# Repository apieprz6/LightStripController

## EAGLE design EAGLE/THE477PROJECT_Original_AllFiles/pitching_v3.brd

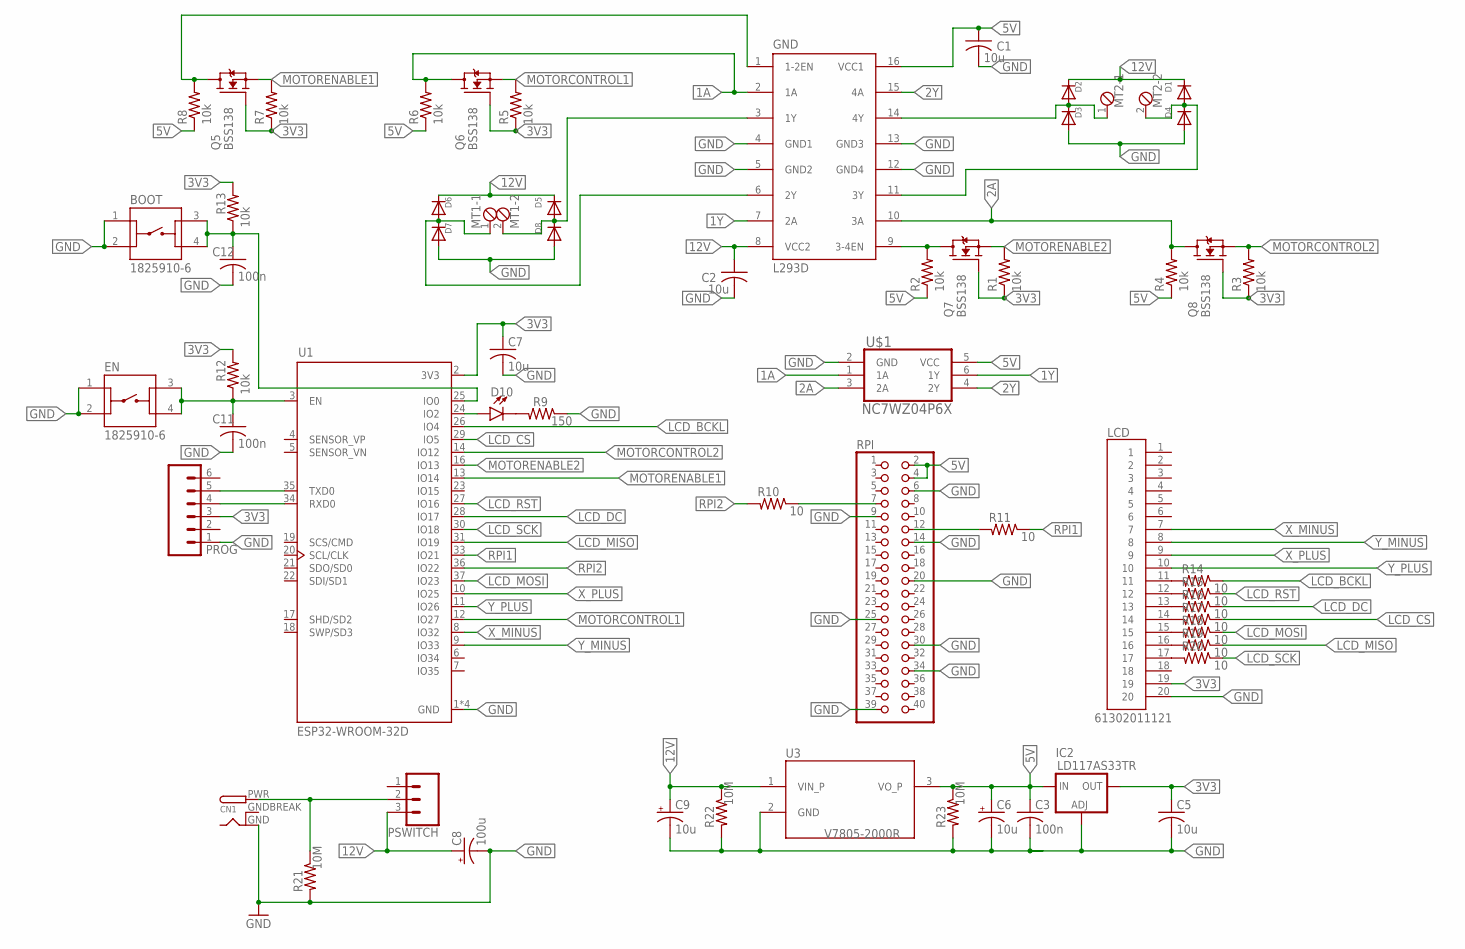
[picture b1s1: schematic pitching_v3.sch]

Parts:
BOOT: 1825910-6
C1, C2, C5, C7: 10u; C0805
C3, C11, C12: 100n; C0805
C6, C9: 10u; 153CLV-0405
C8: 100u; 153CLV-0810
CN1: DCBARRELPTH; DCJACK_2MM_PTH
D1, D2, D3, D4, D5, D6, D7, D8: DIODESMA; SMADIODE
D10: LED3MM; LED_3MM
EN: 1825910-6
GND: L293D; DIL16
IC2: LD117AS33TR; SOT223
LCD: 61302011121
MT1, MT2: MPT2; 2POL254
PROG: CONN_06SILK_FEMALE_PTH; 1X06
PSWITCH: CONN_03; 1X03
Q5, Q6, Q7, Q8: BSS138; SOT23
R1, R2, R3, R4, R5, R6, R7, R8, R12, R13: 10k; R0805
R9: 150; R0805
R10, R11, R14, R15, R16, R17, R18, R19, R20: 10; R0805
R21, R22, R23: 10M; R1206
RPI: PINHD-2X20; 2X20
U1: ESP32-WROOM-32D; MODULE_ESP32-WROOM-32D
U3: V7805-2000R; CONV_V7805-2000R
U$1: NC7WZ04P6X; SOT65P210X110-6N

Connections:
1A: GND.2 (1A), Q6.3 (D), R6.2, U$1.1 (1A)
1Y: GND.7 (2A), U$1.6 (1Y)
2A: GND.10 (3A), Q8.3 (D), R4.2, U$1.3 (2A)
2Y: GND.15 (4A), U$1.4 (2Y)
3V3: C5.1, C7.1, IC2.4 (OUT), LCD.19, PROG.3, Q5.1 (G), Q6.1 (G), Q7.1 (G), Q8.1 (G), R1.1, R3.1, R5.1, R7.1, R12.2, R13.2, U1.2 (3V3)
5V: C1.1, C3.1, C6.+, GND.16 (VCC1), IC2.3 (IN), R2.1, R4.1, R6.1, R8.1, R23.1, RPI.2, RPI.4, U3.3 (VO_P), U$1.5 (VCC)
12V: C2.1, C8.+, C9.+, D1.C, D2.C, D5.C, D6.C, GND.8 (VCC2), PSWITCH.3, R22.1, U3.1 (VIN_P)
BOOT: BOOT.3, BOOT.4, C12.1, R13.1, U1.25 (IO0)
EN: C11.1, EN.3, EN.4, R12.1, U1.3 (EN)
GND: BOOT.1, BOOT.2, C1.2, C2.2, C3.2, C5.2, C6.-, C7.2, C8.-, C9.-, C11.2, C12.2, CN1.GND, D3.A, D4.A, D7.A, D8.A, EN.1, EN.2, GND.4 (GND1), GND.5 (GND2), GND.12 (GND4), GND.13 (GND3), IC2.1 (ADJ), LCD.20, PROG.1, R9.1, R21.2, R22.2, R23.2, RPI.6, RPI.9, RPI.14, RPI.20, RPI.25, RPI.30, RPI.34, RPI.39, U1.1 (GND), U1.15 (GND), U1.38 (GND), U1.39 (GND), U3.2 (GND), U$1.2 (GND)
GNDBREAK: CN1.GNDBREAK
LCD_BCKL: R14.1, U1.26 (IO4)
LCD_CS: R17.1, U1.29 (IO5)
LCD_DC: R16.1, U1.28 (IO17)
LCD_MISO: R19.1, U1.31 (IO19)
LCD_MOSI: R18.1, U1.37 (IO23)
LCD_RST: R15.1, U1.27 (IO16)
LCD_SCK: R20.1, U1.30 (IO18)
M1+: D5.A, D8.C, GND.3 (1Y), MT1.2
M1-: D6.A, D7.C, GND.6 (2Y), MT1.1
M2+: D1.A, D4.C, GND.11 (3Y), MT2.2
M2-: D2.A, D3.C, GND.14 (4Y), MT2.1
MOTORCONTROL1: Q6.2 (S), R5.2, U1.12 (IO27)
MOTORCONTROL2: Q8.2 (S), R3.2, U1.14 (IO12)
MOTORENABLE1: Q5.2 (S), R7.2, U1.13 (IO14)
MOTORENABLE2: Q7.2 (S), R1.2, U1.16 (IO13)
unnamed: CN1.PWR, PSWITCH.2, R21.1
unnamed: R11.2, RPI.12
unnamed: LCD.11, R14.2
unnamed: R10.1, RPI.7
unnamed: LCD.12, R15.2
unnamed: LCD.13, R16.2
unnamed: GND.1 (1-2EN), Q5.3 (D), R8.2
unnamed: GND.9 (3-4EN), Q7.3 (D), R2.2
unnamed: D10.K (C), R9.2
unnamed: LCD.14, R17.2
unnamed: LCD.15, R18.2
unnamed: PROG.5, U1.35 (TXD0)
unnamed: LCD.16, R19.2
unnamed: LCD.17, R20.2
unnamed: PROG.4, U1.34 (RXD0)
unnamed: D10.A, U1.24 (IO2)
RPI1: R11.1, U1.33 (IO21)
RPI2: R10.2, U1.36 (IO22)
X_MINUS: LCD.7, U1.8 (IO32)
X_PLUS: LCD.9, U1.10 (IO25)
Y_MINUS: LCD.8, U1.9 (IO33)
Y_PLUS: LCD.10, U1.11 (IO26)

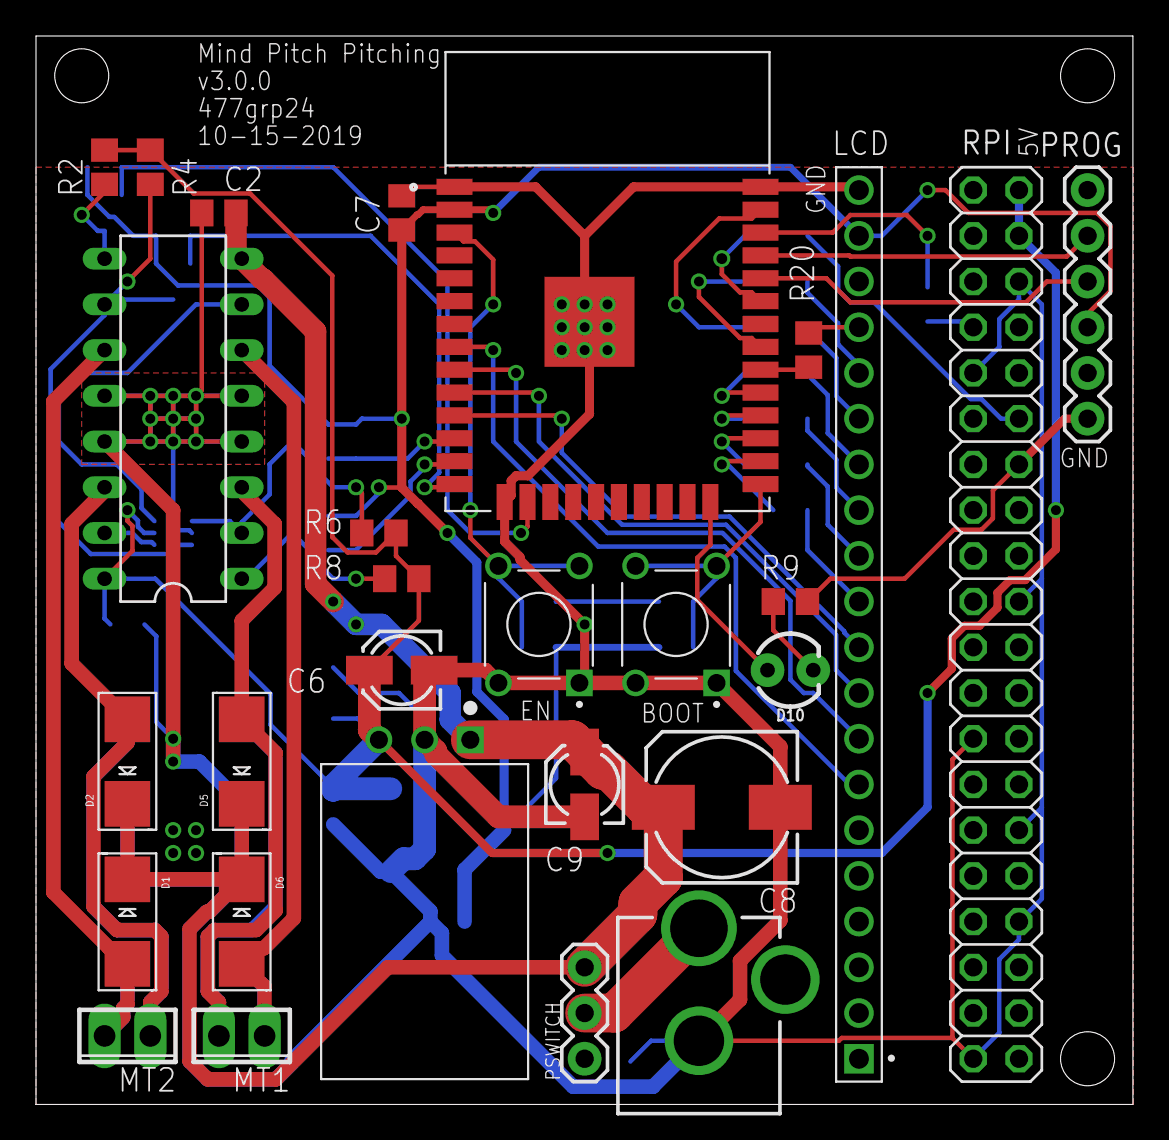
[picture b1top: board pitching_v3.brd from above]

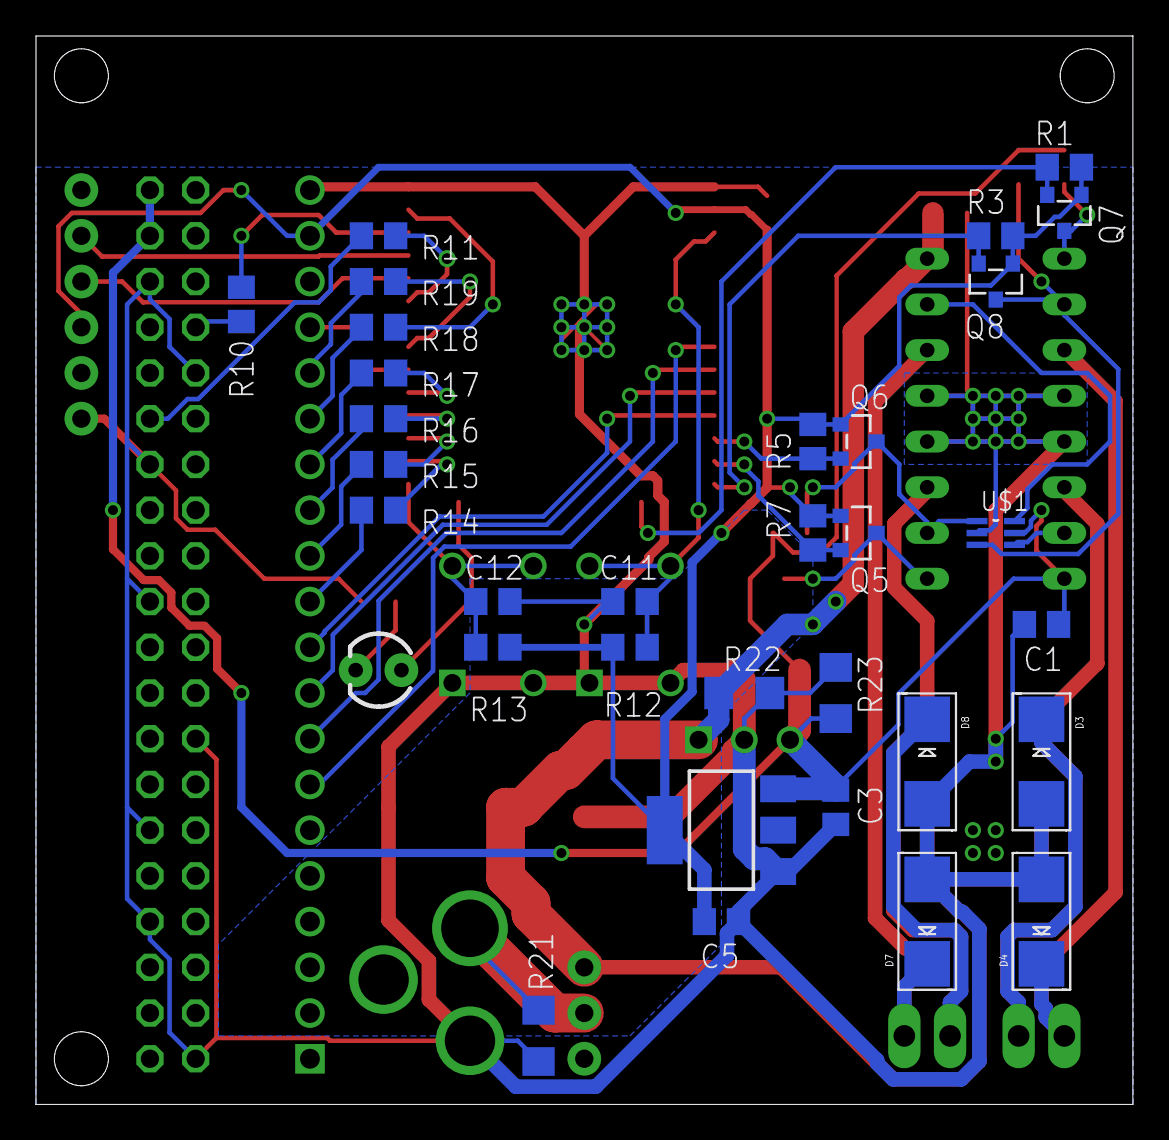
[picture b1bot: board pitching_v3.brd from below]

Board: 2 copper layers, 60.9 x 59.4 mm, 60 parts (32 on the bottom side), 47 nets.

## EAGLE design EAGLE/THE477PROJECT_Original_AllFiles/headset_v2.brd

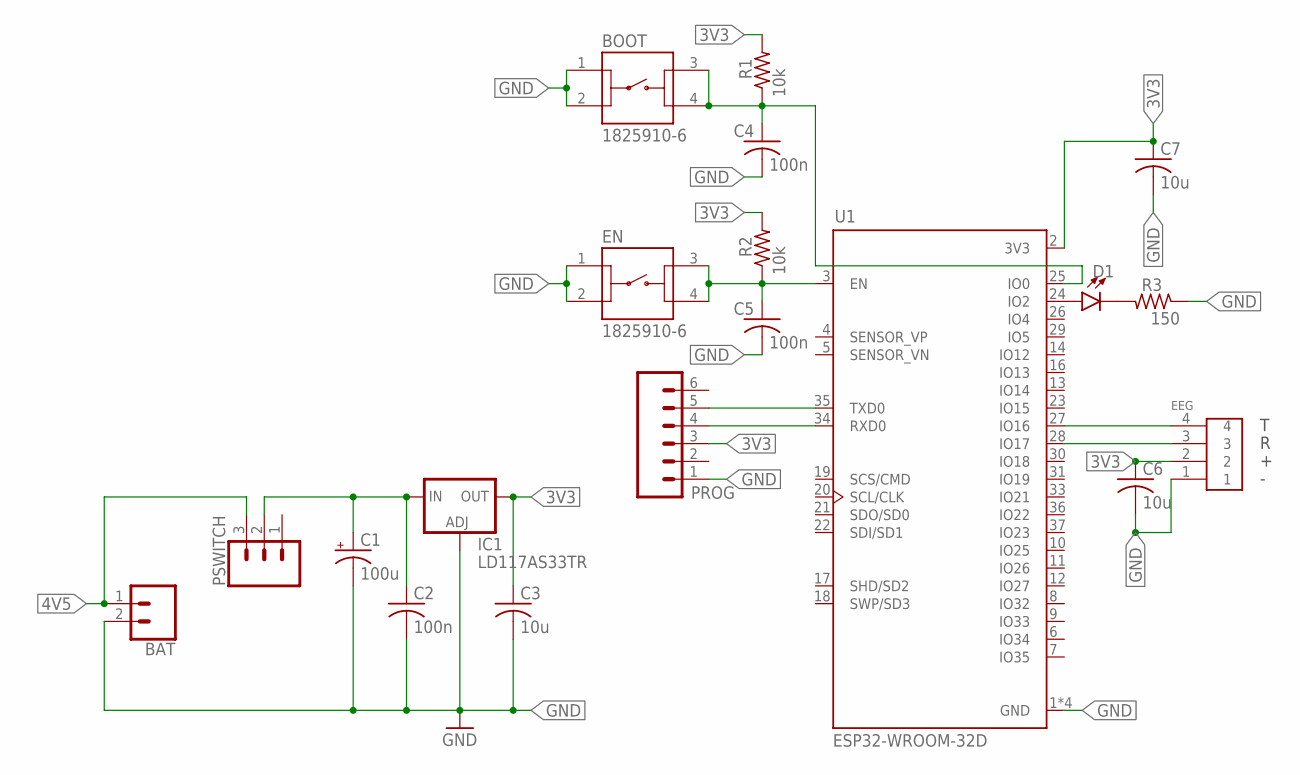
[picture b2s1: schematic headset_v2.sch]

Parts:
BAT: CONN_02; 1X02
BOOT: 1825910-6
C1: 100u; 153CLV-0810
C2, C4, C5: 100n; C0805
C3, C6, C7: 10u; C0805
D1: LED3MM; LED_3MM
EEG: 2PIN; B2B-PH-K-S
EN: 1825910-6
IC1: LD117AS33TR; SOT223
PROG: CONN_06SILK_FEMALE_PTH; 1X06
PSWITCH: CONN_03; 1X03
R1, R2: 10k; R0805
R3: 150; R0805
U1: ESP32-WROOM-32D; MODULE_ESP32-WROOM-32D

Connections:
3V3: C3.1, C6.1, C7.1, EEG.2, IC1.4 (OUT), PROG.3, R1.2, R2.2, U1.2 (3V3)
4V5: BAT.1, PSWITCH.3
GND: BAT.2, BOOT.1, BOOT.2, C1.-, C2.2, C3.2, C4.2, C5.2, C6.2, C7.2, EEG.1, EN.1, EN.2, IC1.1 (ADJ), PROG.1, R3.1, U1.1 (GND), U1.15 (GND), U1.38 (GND), U1.39 (GND)
unnamed: PROG.5, U1.35 (TXD0)
unnamed: PROG.4, U1.34 (RXD0)
unnamed: C1.+, C2.1, IC1.3 (IN), PSWITCH.2
unnamed: D1.A, U1.24 (IO2)
unnamed: EEG.3, U1.28 (IO17)
unnamed: EEG.4, U1.27 (IO16)
unnamed: D1.K (C), R3.2
unnamed: C5.1, EN.3, EN.4, R2.1, U1.3 (EN)
unnamed: BOOT.3, BOOT.4, C4.1, R1.1, U1.25 (IO0)

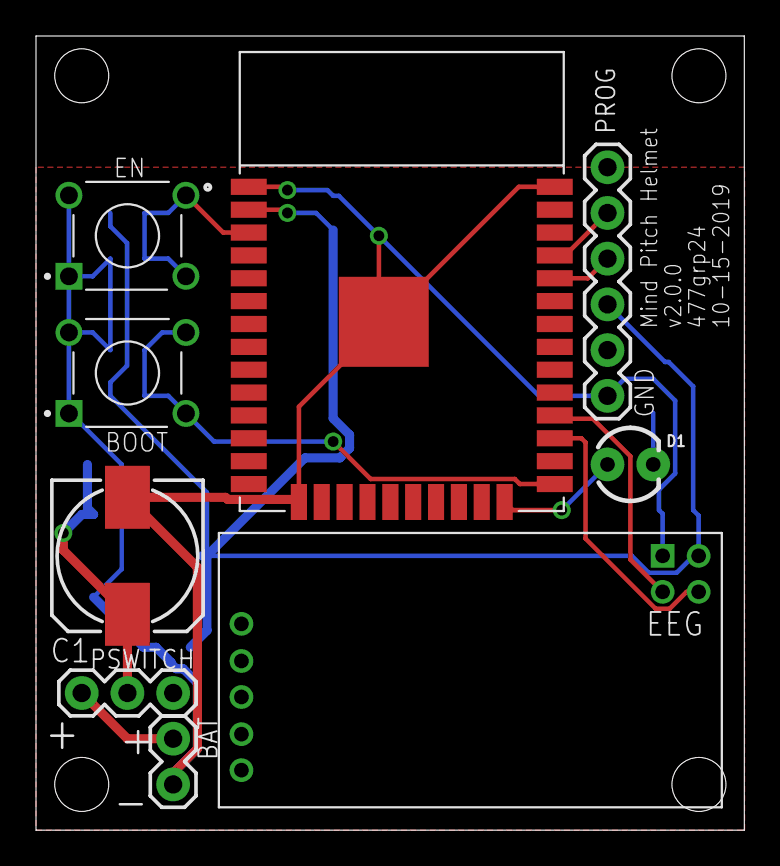
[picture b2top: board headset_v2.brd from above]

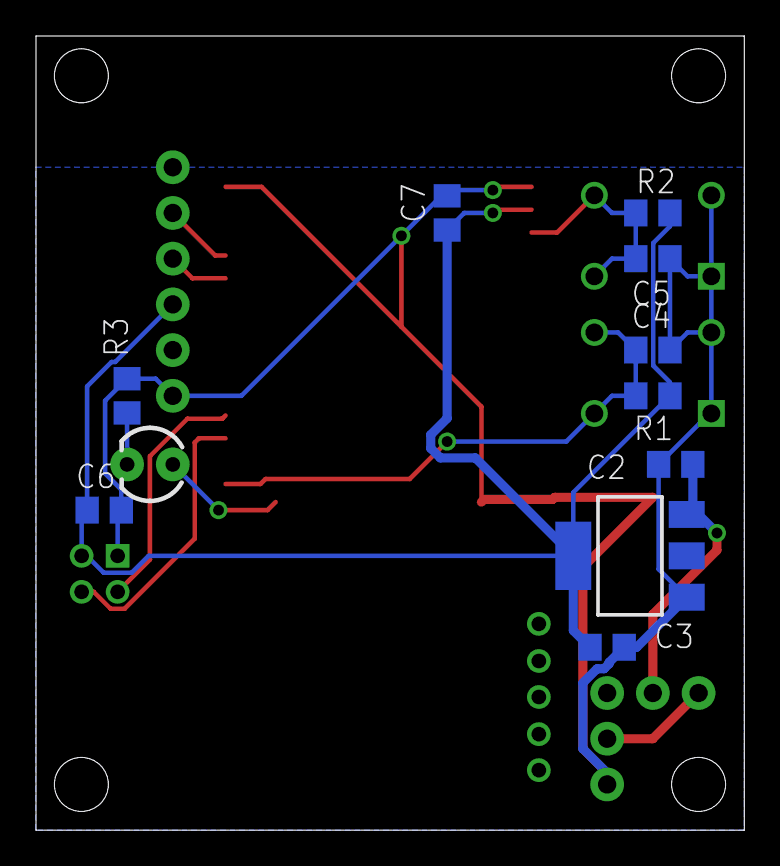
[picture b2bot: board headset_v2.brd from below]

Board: 2 copper layers, 39.4 x 44.1 mm, 19 parts (10 on the bottom side), 12 nets.

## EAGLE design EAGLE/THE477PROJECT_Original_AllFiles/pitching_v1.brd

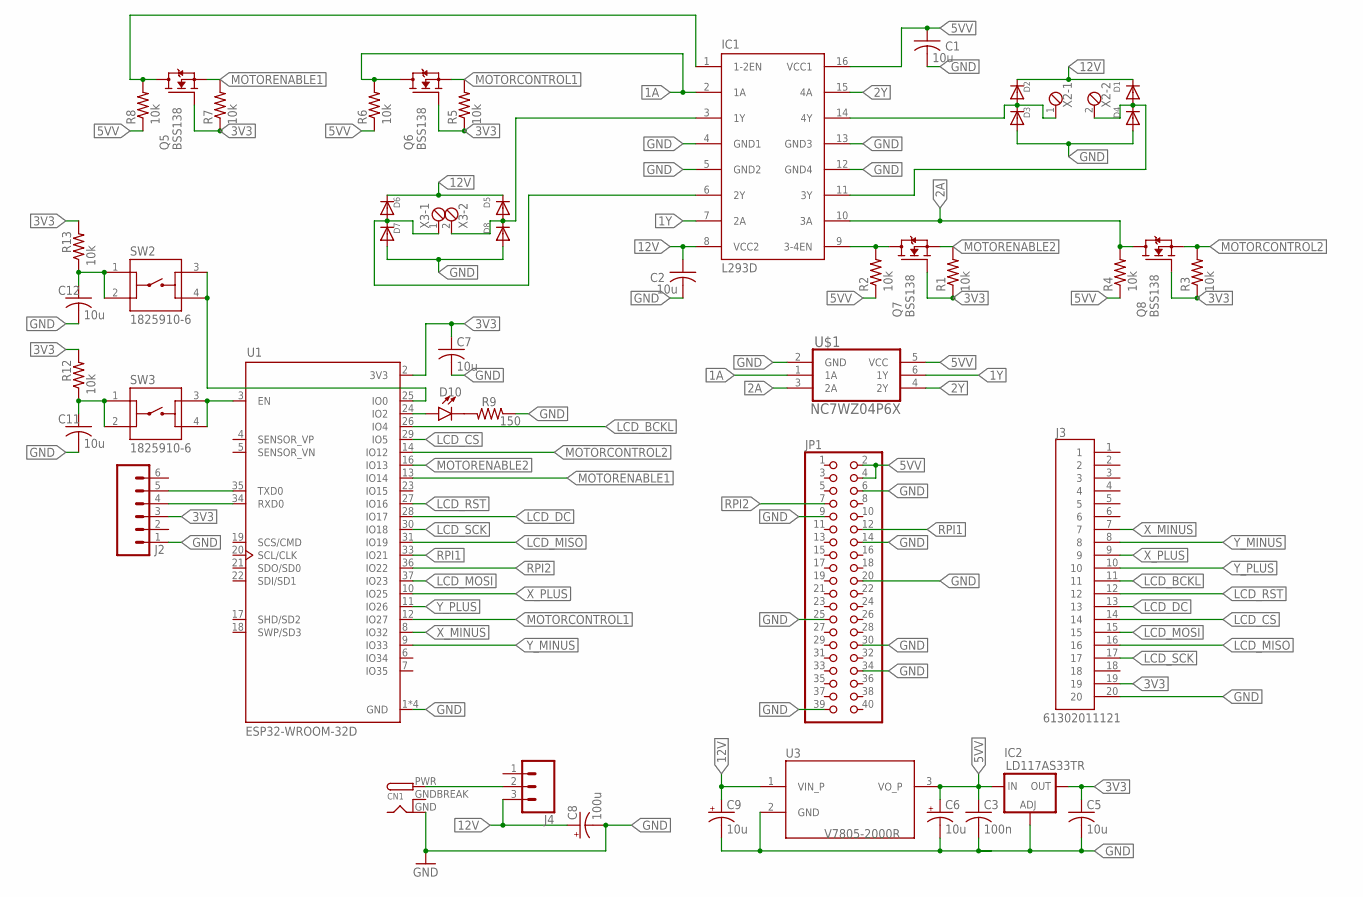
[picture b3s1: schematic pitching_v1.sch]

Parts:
C1, C2, C5, C7, C11, C12: 10u; C0805
C3: 100n; C0805
C6, C9: 10u; 153CLV-0405
C8: 100u; 153CLV-0810
CN1: DCBARRELPTH; DCJACK_2MM_PTH
D1, D2, D3, D4, D5, D6, D7, D8: DIODESMA; SMADIODE
D10: LED3MM; LED_3MM
IC1: L293D; DIL16
IC2: LD117AS33TR; SOT223
J2: CONN_06NO_SILK_FEMALE_PTH; 1X06_NO_SILK
J3: 61302011121
J4: CONN_03; 1X03
JP1: PINHD-2X20; 2X20
Q5, Q6, Q7, Q8: BSS138; SOT23
R1, R2, R3, R4, R5, R6, R7, R8, R12, R13: 10k; R0805
R9: 150; R0805
SW2, SW3: 1825910-6
U1: ESP32-WROOM-32D; MODULE_ESP32-WROOM-32D
U3: V7805-2000R; CONV_V7805-2000R
U$1: NC7WZ04P6X; SOT65P210X110-6N
X2, X3: MPT2; 2POL254

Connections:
1A: IC1.2 (1A), Q6.3 (D), R6.2, U$1.1 (1A)
1Y: IC1.7 (2A), U$1.6 (1Y)
2A: IC1.10 (3A), Q8.3 (D), R4.2, U$1.3 (2A)
2Y: IC1.15 (4A), U$1.4 (2Y)
3V3: C5.1, C7.1, IC2.4 (OUT), J2.3, J3.19, Q5.1 (G), Q6.1 (G), Q7.1 (G), Q8.1 (G), R1.1, R3.1, R5.1, R7.1, R12.2, R13.2, U1.2 (3V3)
5VV: C1.1, C3.1, C6.+, IC1.16 (VCC1), IC2.3 (IN), JP1.2, JP1.4, R2.1, R4.1, R6.1, R8.1, U3.3 (VO_P), U$1.5 (VCC)
12V: C2.1, C8.+, C9.+, D1.C, D2.C, D5.C, D6.C, IC1.8 (VCC2), J4.3, U3.1 (VIN_P)
GND: C1.2, C2.2, C3.2, C5.2, C6.-, C7.2, C8.-, C9.-, C11.2, C12.2, CN1.GND, D3.A, D4.A, D7.A, D8.A, IC1.4 (GND1), IC1.5 (GND2), IC1.12 (GND4), IC1.13 (GND3), IC2.1 (ADJ), J2.1, J3.20, JP1.6, JP1.9, JP1.14, JP1.20, JP1.25, JP1.30, JP1.34, JP1.39, R9.1, U1.1 (GND), U1.15 (GND), U1.38 (GND), U1.39 (GND), U3.2 (GND), U$1.2 (GND)
GNDBREAK: CN1.GNDBREAK
LCD_BCKL: J3.11, U1.26 (IO4)
LCD_CS: J3.14, U1.29 (IO5)
LCD_DC: J3.13, U1.28 (IO17)
LCD_MISO: J3.16, U1.31 (IO19)
LCD_MOSI: J3.15, U1.37 (IO23)
LCD_RST: J3.12, U1.27 (IO16)
LCD_SCK: J3.17, U1.30 (IO18)
MOTORCONTROL1: Q6.2 (S), R5.2, U1.12 (IO27)
MOTORCONTROL2: Q8.2 (S), R3.2, U1.14 (IO12)
MOTORENABLE1: Q5.2 (S), R7.2, U1.13 (IO14)
MOTORENABLE2: Q7.2 (S), R1.2, U1.16 (IO13)
unnamed: CN1.PWR, J4.2
unnamed: D6.A, D7.C, IC1.6 (2Y), X3.1
unnamed: D5.A, D8.C, IC1.3 (1Y), X3.2
unnamed: D2.A, D3.C, IC1.14 (4Y), X2.1
unnamed: D1.A, D4.C, IC1.11 (3Y), X2.2
unnamed: IC1.1 (1-2EN), Q5.3 (D), R8.2
unnamed: IC1.9 (3-4EN), Q7.3 (D), R2.2
unnamed: SW2.3, SW2.4, U1.25 (IO0)
unnamed: D10.K (C), R9.2
unnamed: J2.5, U1.35 (TXD0)
unnamed: J2.4, U1.34 (RXD0)
unnamed: C11.1, R12.1, SW3.1, SW3.2
unnamed: C12.1, R13.1, SW2.1, SW2.2
unnamed: D10.A, U1.24 (IO2)
unnamed: SW3.3, SW3.4, U1.3 (EN)
RPI1: JP1.12, U1.33 (IO21)
RPI2: JP1.7, U1.36 (IO22)
X_MINUS: J3.7, U1.8 (IO32)
X_PLUS: J3.9, U1.10 (IO25)
Y_MINUS: J3.8, U1.9 (IO33)
Y_PLUS: J3.10, U1.11 (IO26)

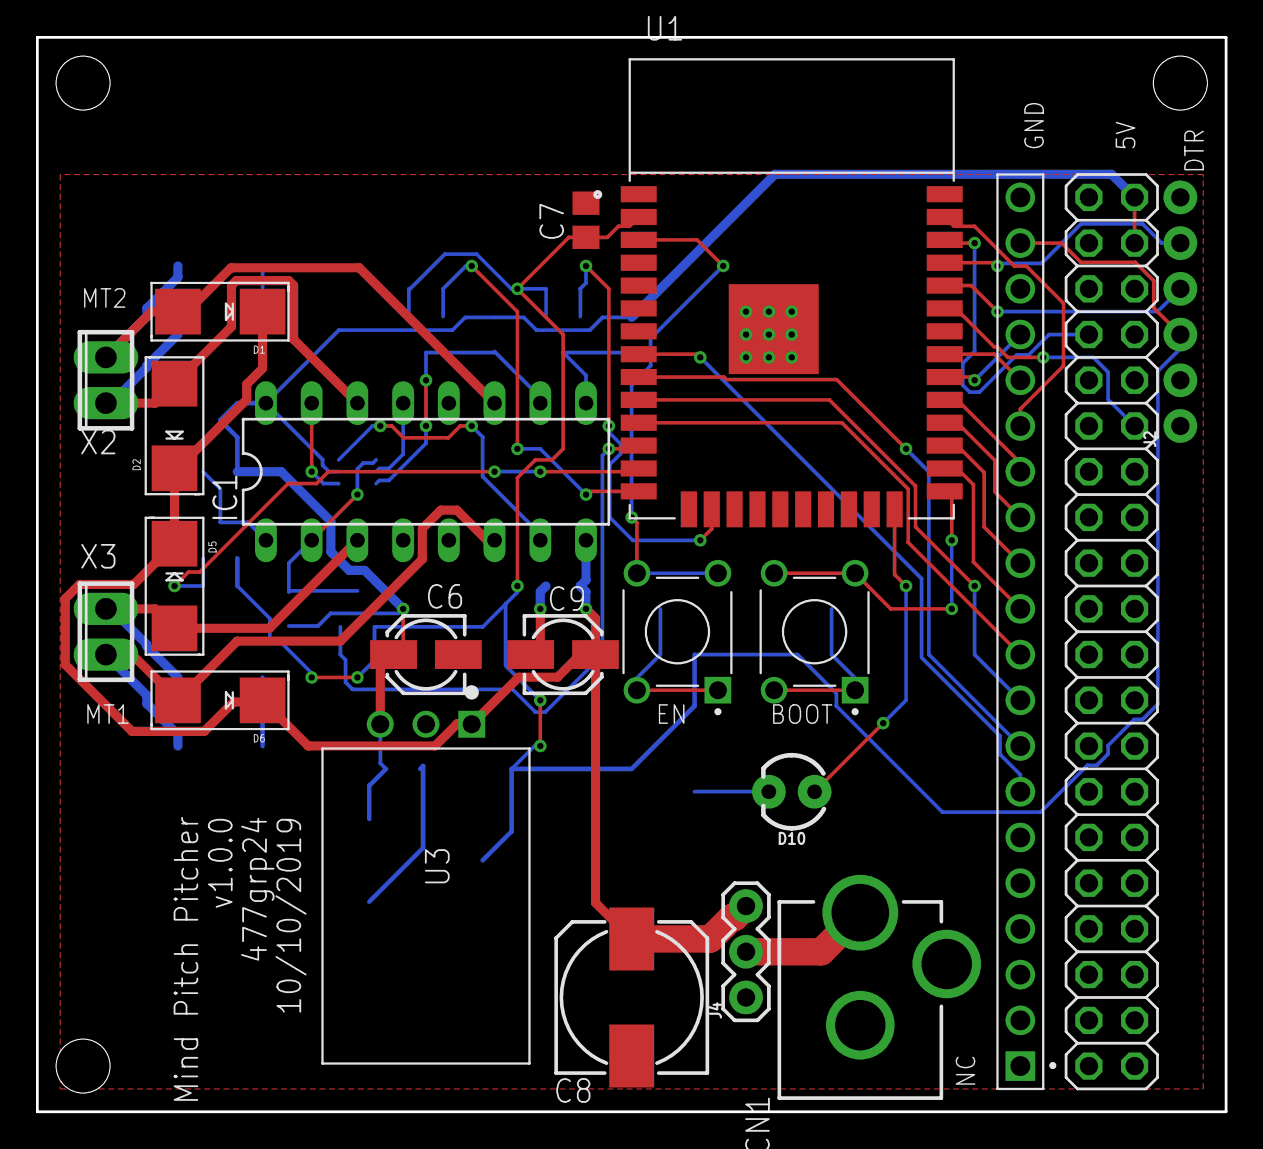
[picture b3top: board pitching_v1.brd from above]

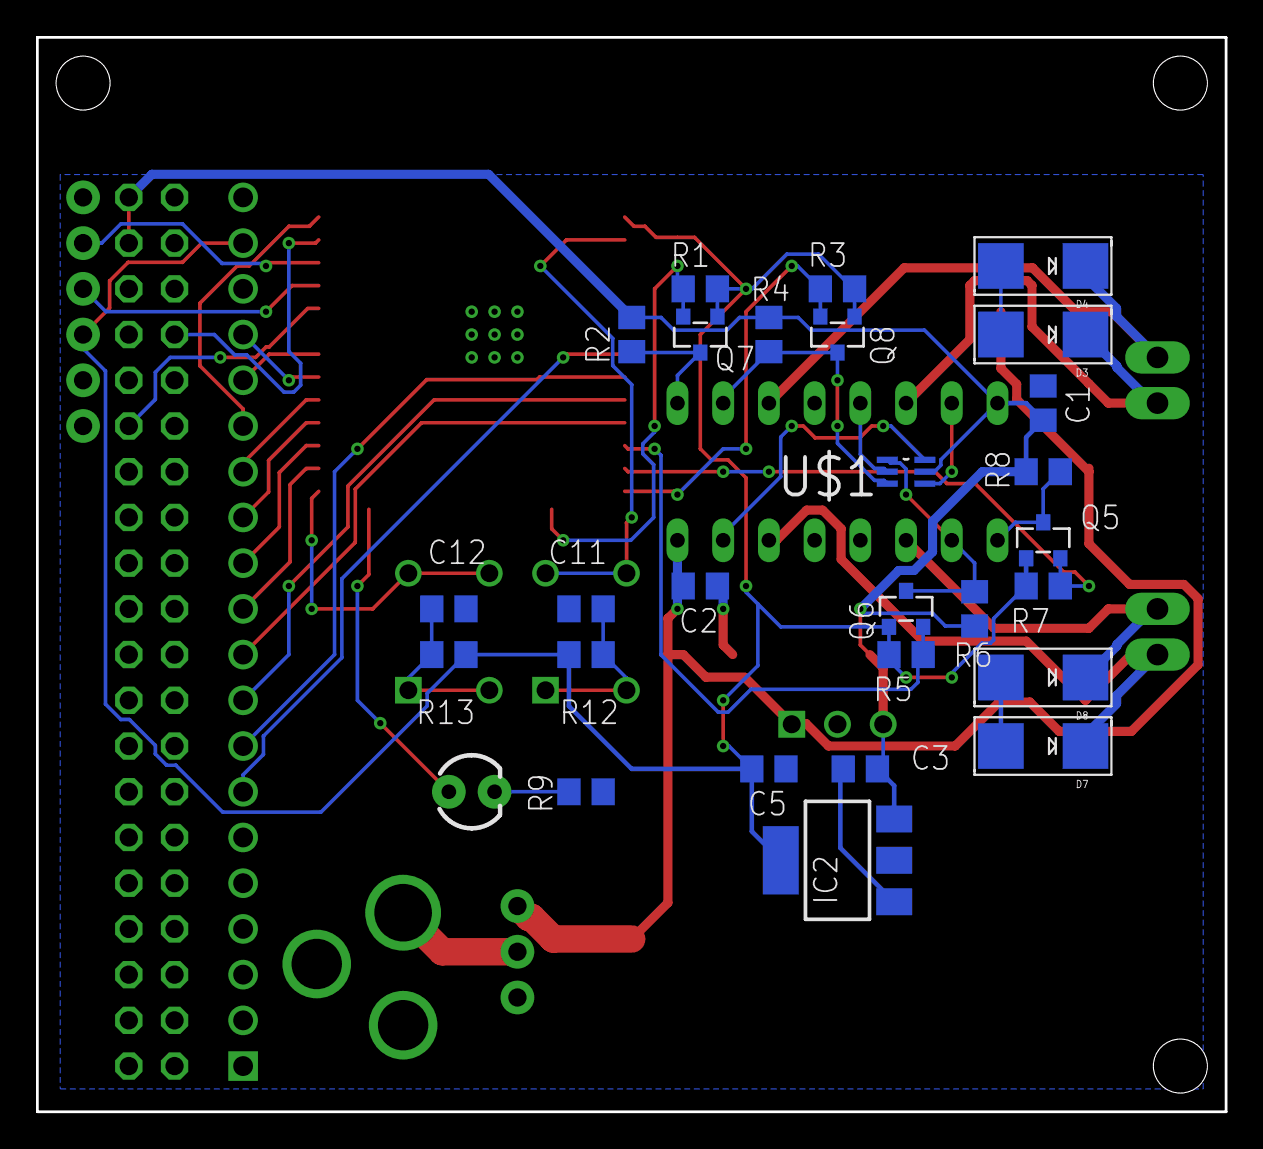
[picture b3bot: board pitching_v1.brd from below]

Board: 2 copper layers, 66.0 x 59.7 mm, 48 parts (27 on the bottom side), 40 nets.

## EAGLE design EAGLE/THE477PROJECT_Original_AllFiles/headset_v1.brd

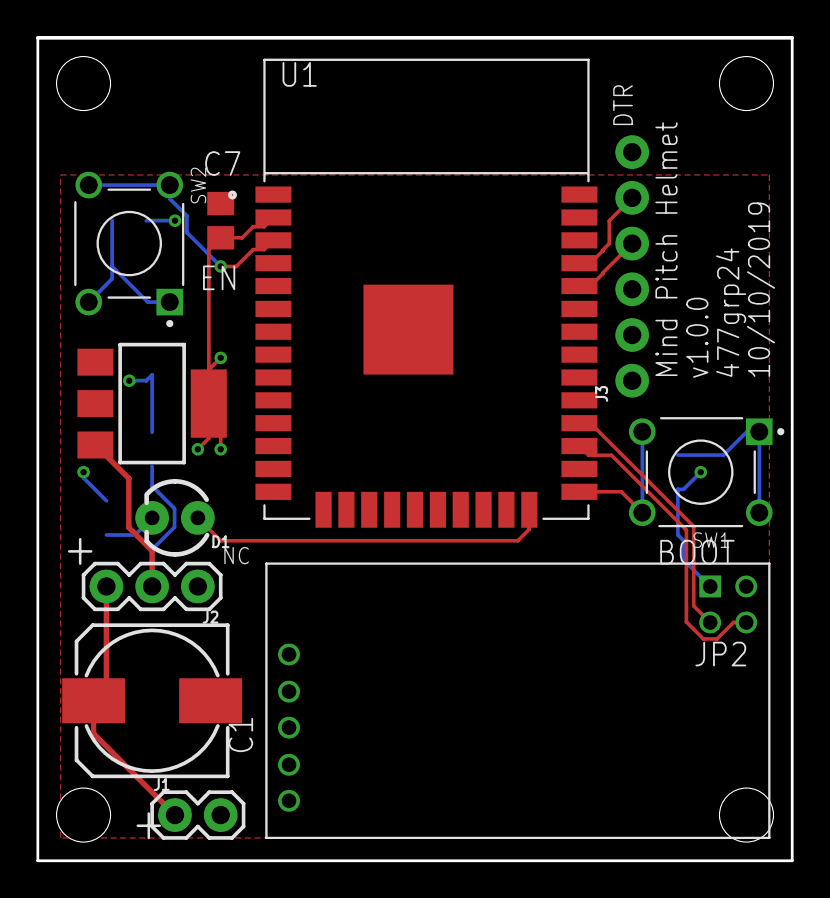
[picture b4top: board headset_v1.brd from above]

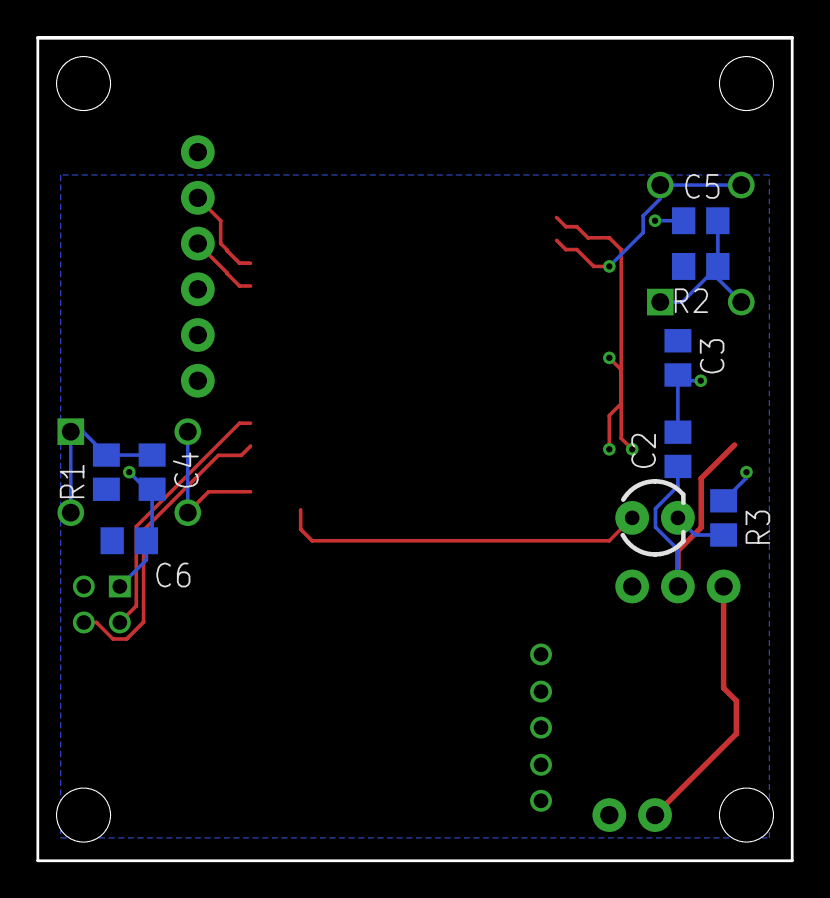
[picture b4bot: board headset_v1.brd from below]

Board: 2 copper layers, 41.9 x 45.7 mm, 19 parts (8 on the bottom side), 14 nets.

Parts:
C1: 100u; 153CLV-0810
C2: 100n; C0805
C3, C4, C5, C6, C7: 10u; C0805
D1: LED_3MM
IC1: LD117AS33TR; SOT223
J1: 1X02
J2: 1X03
J3: 1X06_NO_SILK
JP2: 2PIN; B2B-PH-K-S
R1, R2: 10k; R0805
R3: 150; R0805
SW1, SW2: 1825910-6
U1: ESP32-WROOM-32D; MODULE_ESP32-WROOM-32D

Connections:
3V3: C3.1, C6.1, C7.1, IC1.4, J3.3, JP2.2, R1.2, R2.2, U1.2
4V5: C1.+, J1.1, J2.3
GND: C1.-, C2.2, C3.2, C4.2, C5.2, C6.2, C7.2, IC1.1, J1.2, J3.1, JP2.1, R3.1, U1.1, U1.15, U1.38, U1.39
unnamed: J3.5, U1.35
unnamed: J3.4, U1.34
unnamed: C2.1, IC1.3, J2.2
unnamed: D1.A, U1.24
unnamed: JP2.3, U1.28
unnamed: JP2.4, U1.27
unnamed: C4.1, R1.1, SW1.1, SW1.2
unnamed: SW1.3, SW1.4, U1.25
unnamed: D1.K, R3.2
unnamed: SW2.3, SW2.4, U1.3
unnamed: C5.1, R2.1, SW2.1, SW2.2

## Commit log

2020-05-06 added starting point for pcb
2020-05-26 lots of progress on v2
2020-06-03 lots of progress
2020-08-11 added fft code

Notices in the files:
parts and their libraries:
SparkFun-LED: Licensing: Creative Commons ShareAlike 4.0 International - https://creativecommons.org/licenses/by-sa/4.0
